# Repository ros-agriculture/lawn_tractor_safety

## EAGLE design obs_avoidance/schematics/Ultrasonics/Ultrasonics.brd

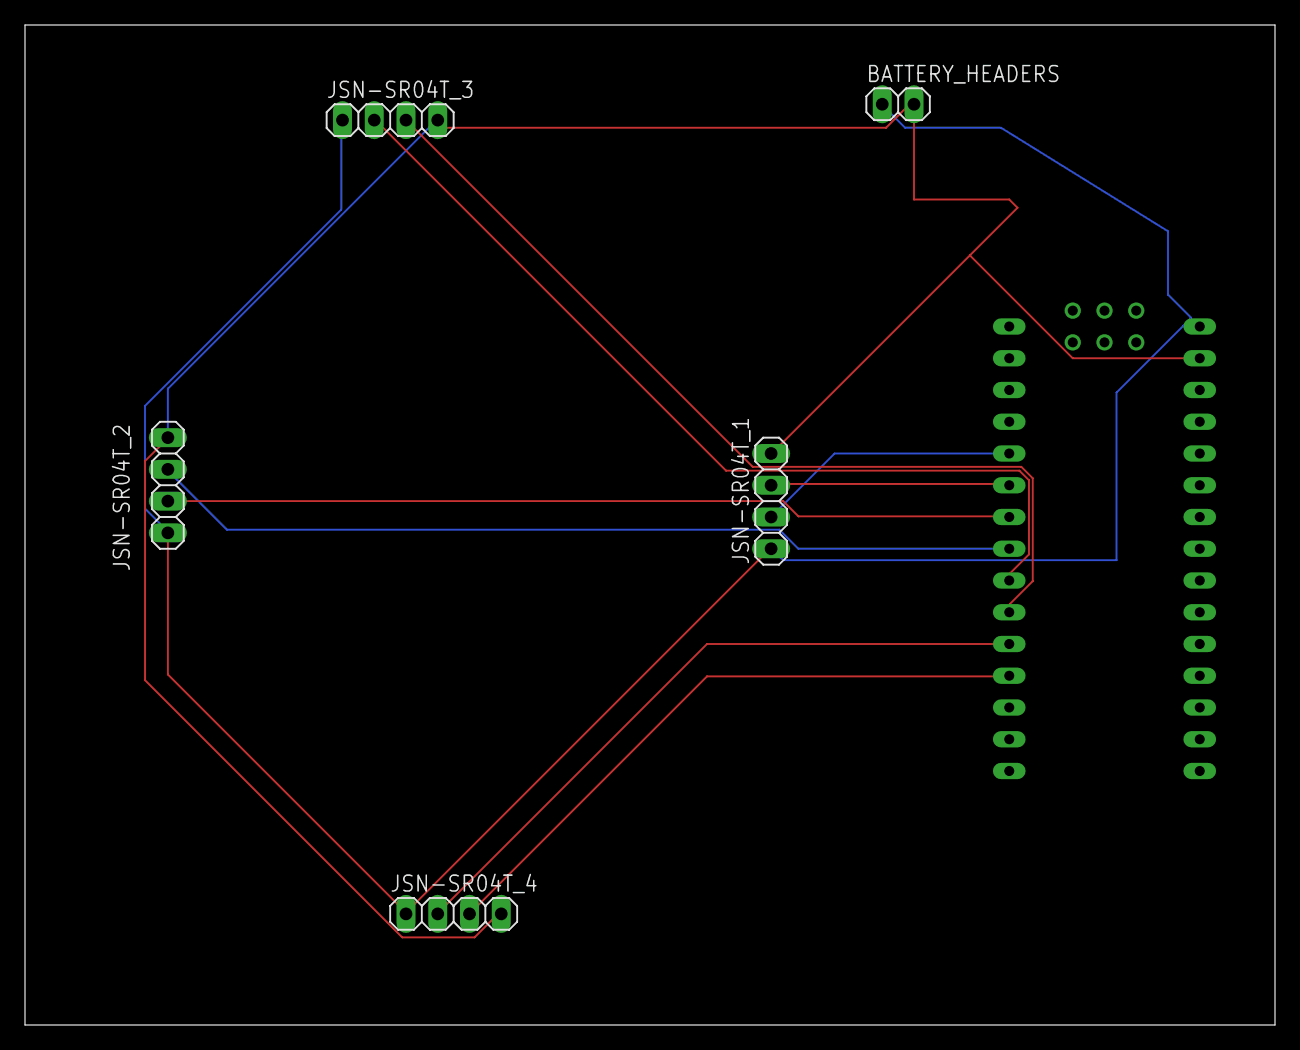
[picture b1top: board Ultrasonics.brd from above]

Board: 2 copper layers, 100.0 x 80.0 mm, 6 parts (0 on the bottom side), 10 nets.

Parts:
BATTERY_HEADERS: 1X02
JSN-SR04T_1, JSN-SR04T_2, JSN-SR04T_3, JSN-SR04T_4: 1X04
U$1: NANO

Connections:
unnamed: BATTERY_HEADERS.1, JSN-SR04T_1.1, JSN-SR04T_2.1, JSN-SR04T_3.1, JSN-SR04T_4.1, U$1.RAW
unnamed: BATTERY_HEADERS.2, JSN-SR04T_1.4, JSN-SR04T_2.4, JSN-SR04T_3.4, JSN-SR04T_4.4, U$1.GND
unnamed: JSN-SR04T_1.2, U$1.D2
unnamed: JSN-SR04T_1.3, U$1.D3
unnamed: JSN-SR04T_2.2, U$1.D4
unnamed: JSN-SR04T_2.3, U$1.D5
unnamed: JSN-SR04T_3.2, U$1.D6
unnamed: JSN-SR04T_3.3, U$1.D7
unnamed: JSN-SR04T_4.2, U$1.D8
unnamed: JSN-SR04T_4.3, U$1.D9

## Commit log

2019-06-07 Add obstacle avoidance design and software
2019-06-07 Docs for obs_avoidance
2019-06-09 Added DC-DC converter to the board
